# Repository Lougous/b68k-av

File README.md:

# Overview

This board provides audio and video capabilities to the b68k computer. Main components:
* CPLD for local bus decoding and FPGA configuration
* [flex FPGA](/doc/flex.md)
* SRAM 16-bits, 256kiB or 512 kiB
* video RAMDAC
* OPL2 audio chip

external interfaces: video (VGA, DIN 15 pins) and audio (3.5mm jack) 

# Memory mapping

The AVMGR CPLD decodes local bus accesses to address itself, the RAMDAC, the OPL2 or the flex FPGA.

| address range     | size   | memory area |
|:-----------------:|:------:|:-----:|
| 00000h  - 0007Fh  | 128B   | AVMGR registers. address bit 0 is ignored |
| 00080h  - 000FFh  | 128B   | flex registers |
| 00100h  - 0017Fh  | 128B   | RAMDAC registers. address bit 0 is ignored |
| 00180h  - 001FFh  | 128B   | OPL2 registers. address bit 0 is ignored |
| 00200h  - 07FFFh  | 512B*63 | mirrors x63 address range 000h-1FFh |
| 08000h -  0FFFFh  | 32kiB   | SRAM access (upper 32kiB, banking through flex register) |
| 10000h -  1FFFFh  | 64kiB   | SRAM access (banking through flex register) |

## AVMGR registers

These registers provide an interface to configure the flex FPGA. Address bit 0 is ignored, so that odd address target the same register as at even address.

| address offset    | name   | description |
|:-----------------:|:------:|:-----
| 00000h            | cfgnsts | bit 0: (r) flex nSTATUS signal<br>bit 1: (r) flex CONF_DONE signal<br>bit 6: (rw) flex nCONFIG signal<br>bit 7: (rw) flex reset signal (active low) |
| 00002h            | dat | bit 0: (rw) flex DAT0 signal<br>When this register is written, the flex DAT0 signal is driven and a pulse is generated on DCLK |
| 00004h            | dbg0 | spare register for debug purpose |
| 00006h            | dbg1 | spare register for debug purpose |

These registers mirror every 8 bytes.

## OPL2 registers

Provide access to the 2 OPL2 registers. Address bit 0 is ignored, so that odd address target the same register as at even address.

| address offset    | name   | description |
|:-----------------:|:------:|:-----
| 00000h            | regad | OPL2 Address (write) and status (read) register |
| 00002h            | regdt | OPL2 Data register |

## RAMDAC registers

Provide access to the RAMDAC registers (Bt476 / IMS G176 or compatible). Address bit 0 is ignored, so that odd address target the same register as at even address.

| address offset    | name   | description |
|:-----------------:|:------:|:-----
| 00000h            | ad_write | Address Register (RAM Write Mode) |
| 00002h            | color | Color Palette RAM |
| 00004h            | mask | Pixel read Mask Register |
| 00006h            | ad_read | Address Register (RAM Read Mode) |

## flex registers

See [flex FPGA](/doc/flex.md) documentation.

# BOM

| Reference  | Part |
|:-----------------:|:------:|
| RN1 | not populated |
| U1 | 74F245 |
| U2 | EPM7064SLC44-10 |
| U3 | MPC6002 |
| U4 | LM337 |
| U6 | EPF10K10LC84-4 |
| U7, U8 | 74F373 |
| U11 | YM3812 (OPL2) |
| U12 | KDA0476BCN-66 |
| D5 | BAT48 (shottky) |
| X1 or X3 | 25-MHz |

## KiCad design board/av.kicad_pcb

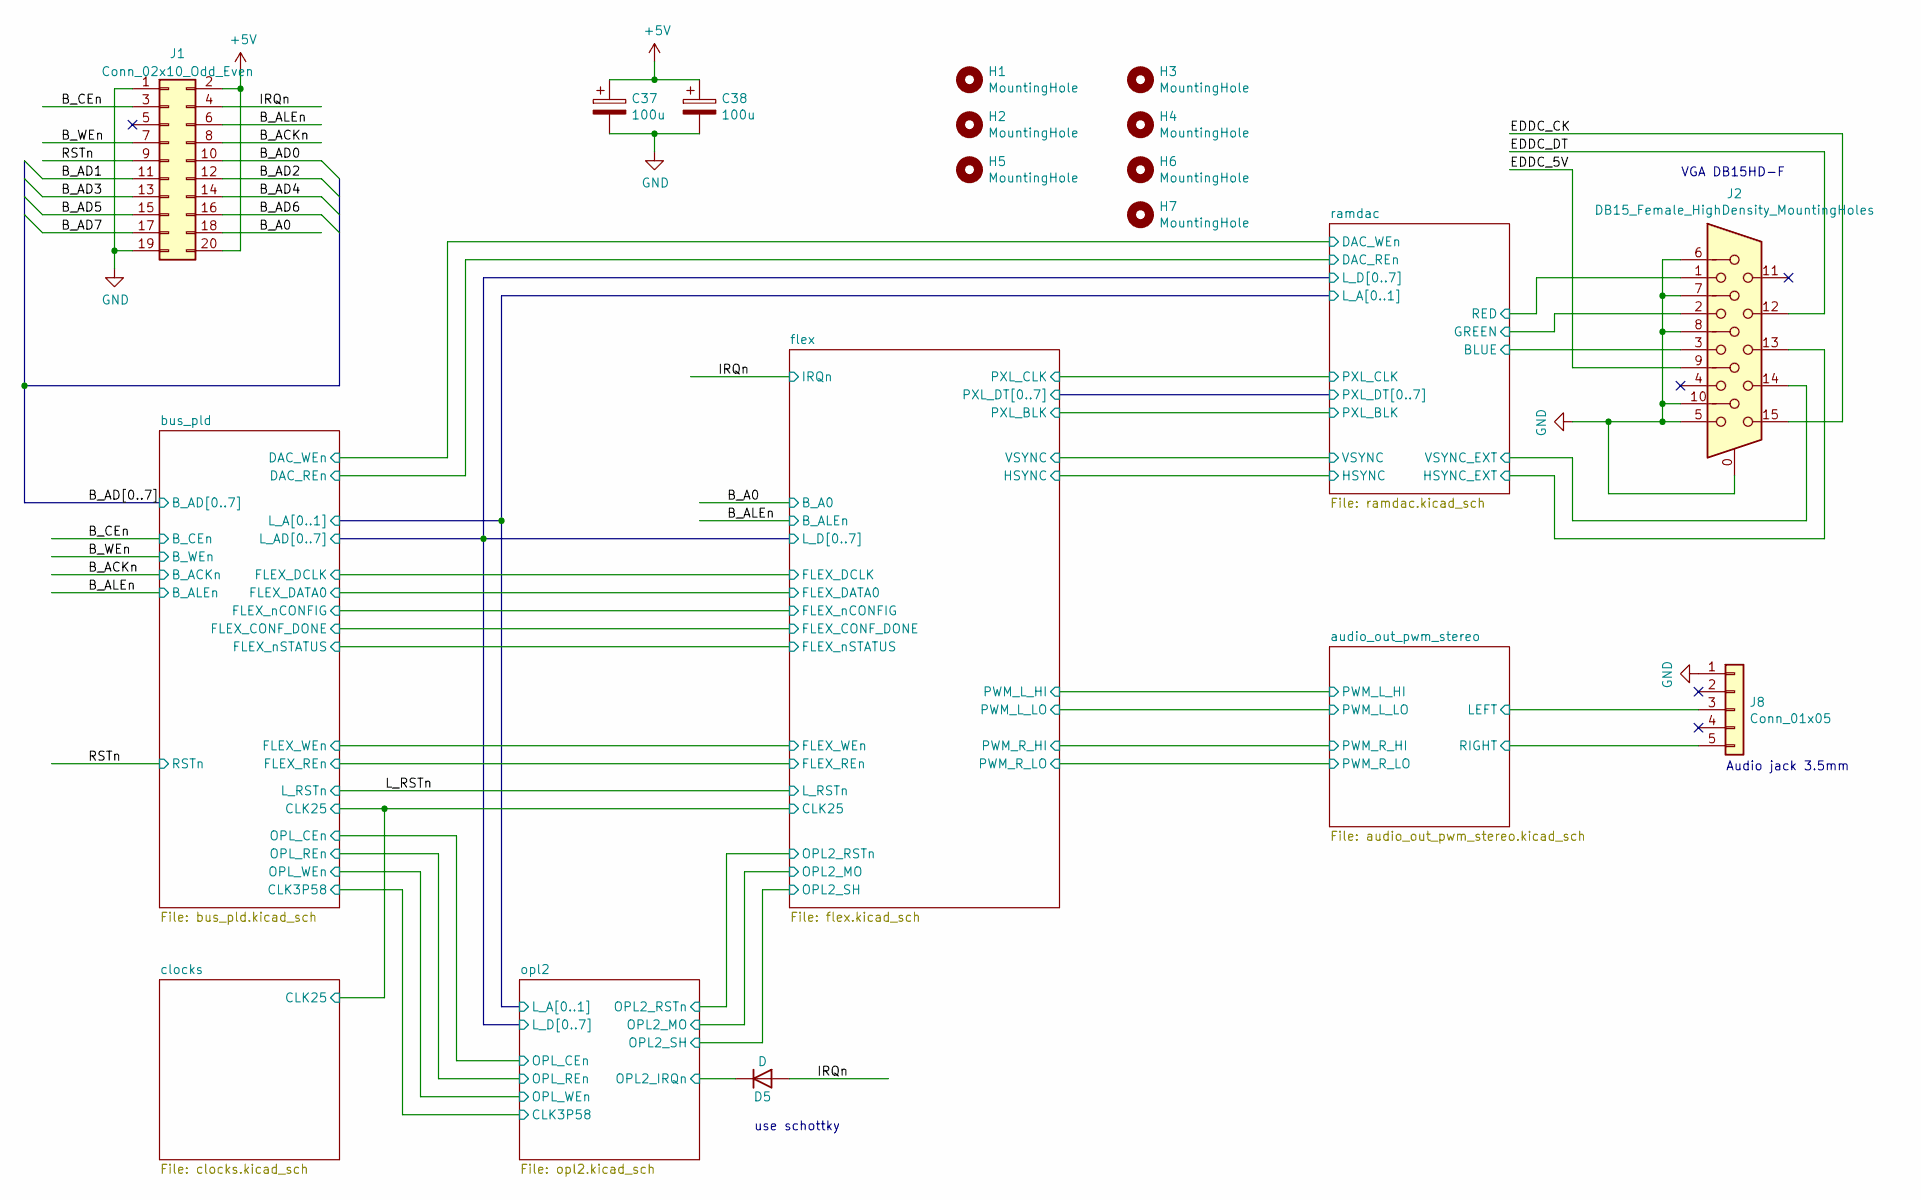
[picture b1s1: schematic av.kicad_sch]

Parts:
C37, C38: 100u; CP_Radial_D5.0mm_P2.00mm
D5: D; D_DO-34_SOD68_P7.62mm_Horizontal
H1, H2, H3, H4, H5, H6, H7: MountingHole; MountingHole_2.7mm_M2.5_DIN965_Pad
J1: Conn_02x10_Odd_Even; PinHeader_2x10_P2.54mm_Vertical
J2: DB15_Female_HighDensity_MountingHoles; DSUB-15-HD_Female_Horizontal_P2.29x1.98mm_EdgePinOffset3.03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
J8: Conn_01x05; ASJ-5-X_3.5mm_Jack

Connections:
+5V: C37.1, C38.1, J1.2, J1.20; also elsewhere on the board
/B_A0: J1.18; also elsewhere on the board
/B_ACKn: J1.8; also elsewhere on the board
/B_AD0: J1.10; also elsewhere on the board
/B_AD1: J1.11; also elsewhere on the board
/B_AD2: J1.12; also elsewhere on the board
/B_AD3: J1.13; also elsewhere on the board
/B_AD4: J1.14; also elsewhere on the board
/B_AD5: J1.15; also elsewhere on the board
/B_AD6: J1.16; also elsewhere on the board
/B_AD7: J1.17; also elsewhere on the board
/B_ALEn: J1.6; also elsewhere on the board
/B_CEn: J1.3; also elsewhere on the board
/B_WEn: J1.7; also elsewhere on the board
/EDDC_5V: J2.9
/EDDC_CK: J2.15
/EDDC_DT: J2.12
/IRQn: D5.2 (A), J1.4; also elsewhere on the board
/RSTn: J1.9; also elsewhere on the board
/audio_out_pwm_stereo/LEFT: J8.3; also elsewhere on the board
/audio_out_pwm_stereo/RIGHT: J8.5; also elsewhere on the board
/opl2/OPL2_IRQn: D5.1 (K); also elsewhere on the board
/ramdac/BLUE: J2.3; also elsewhere on the board
/ramdac/GREEN: J2.2; also elsewhere on the board
/ramdac/HSYNC_EXT: J2.13; also elsewhere on the board
/ramdac/RED: J2.1; also elsewhere on the board
/ramdac/VSYNC_EXT: J2.14; also elsewhere on the board
GND: C37.2, C38.2, J1.1, J1.19, J2.0, J2.5, J2.6, J2.7, J2.8, J2.10, J8.1; also elsewhere on the board

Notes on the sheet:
Audio jack 3.5mm
use schottky
VGA DB15HD-F

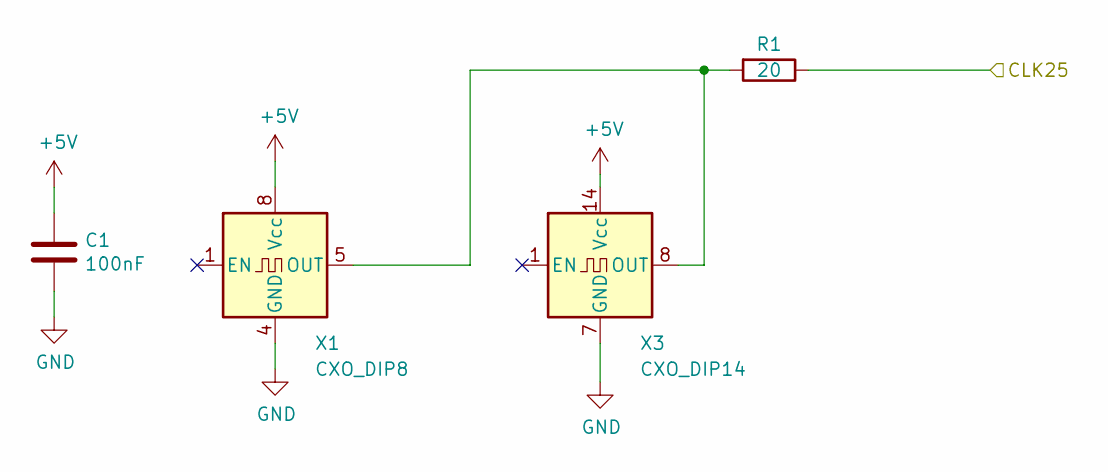
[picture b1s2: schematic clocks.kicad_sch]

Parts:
C1: 100nF; C_Disc_D4.3mm_W1.9mm_P5.00mm
R1: 20; R_Axial_DIN0204_L3.6mm_D1.6mm_P7.62mm_Horizontal
X1: CXO_DIP8; Oscillator_DIP-8
X3: CXO_DIP14; Oscillator_DIP-14

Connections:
+5V: C1.1, X1.8 (Vcc), X3.14 (Vcc); also elsewhere on the board
/flex/CLK25: R1.1; also elsewhere on the board
GND: C1.2, X1.4 (GND), X3.7 (GND); also elsewhere on the board
unnamed: R1.2, X1.5 (OUT), X3.8 (OUT)

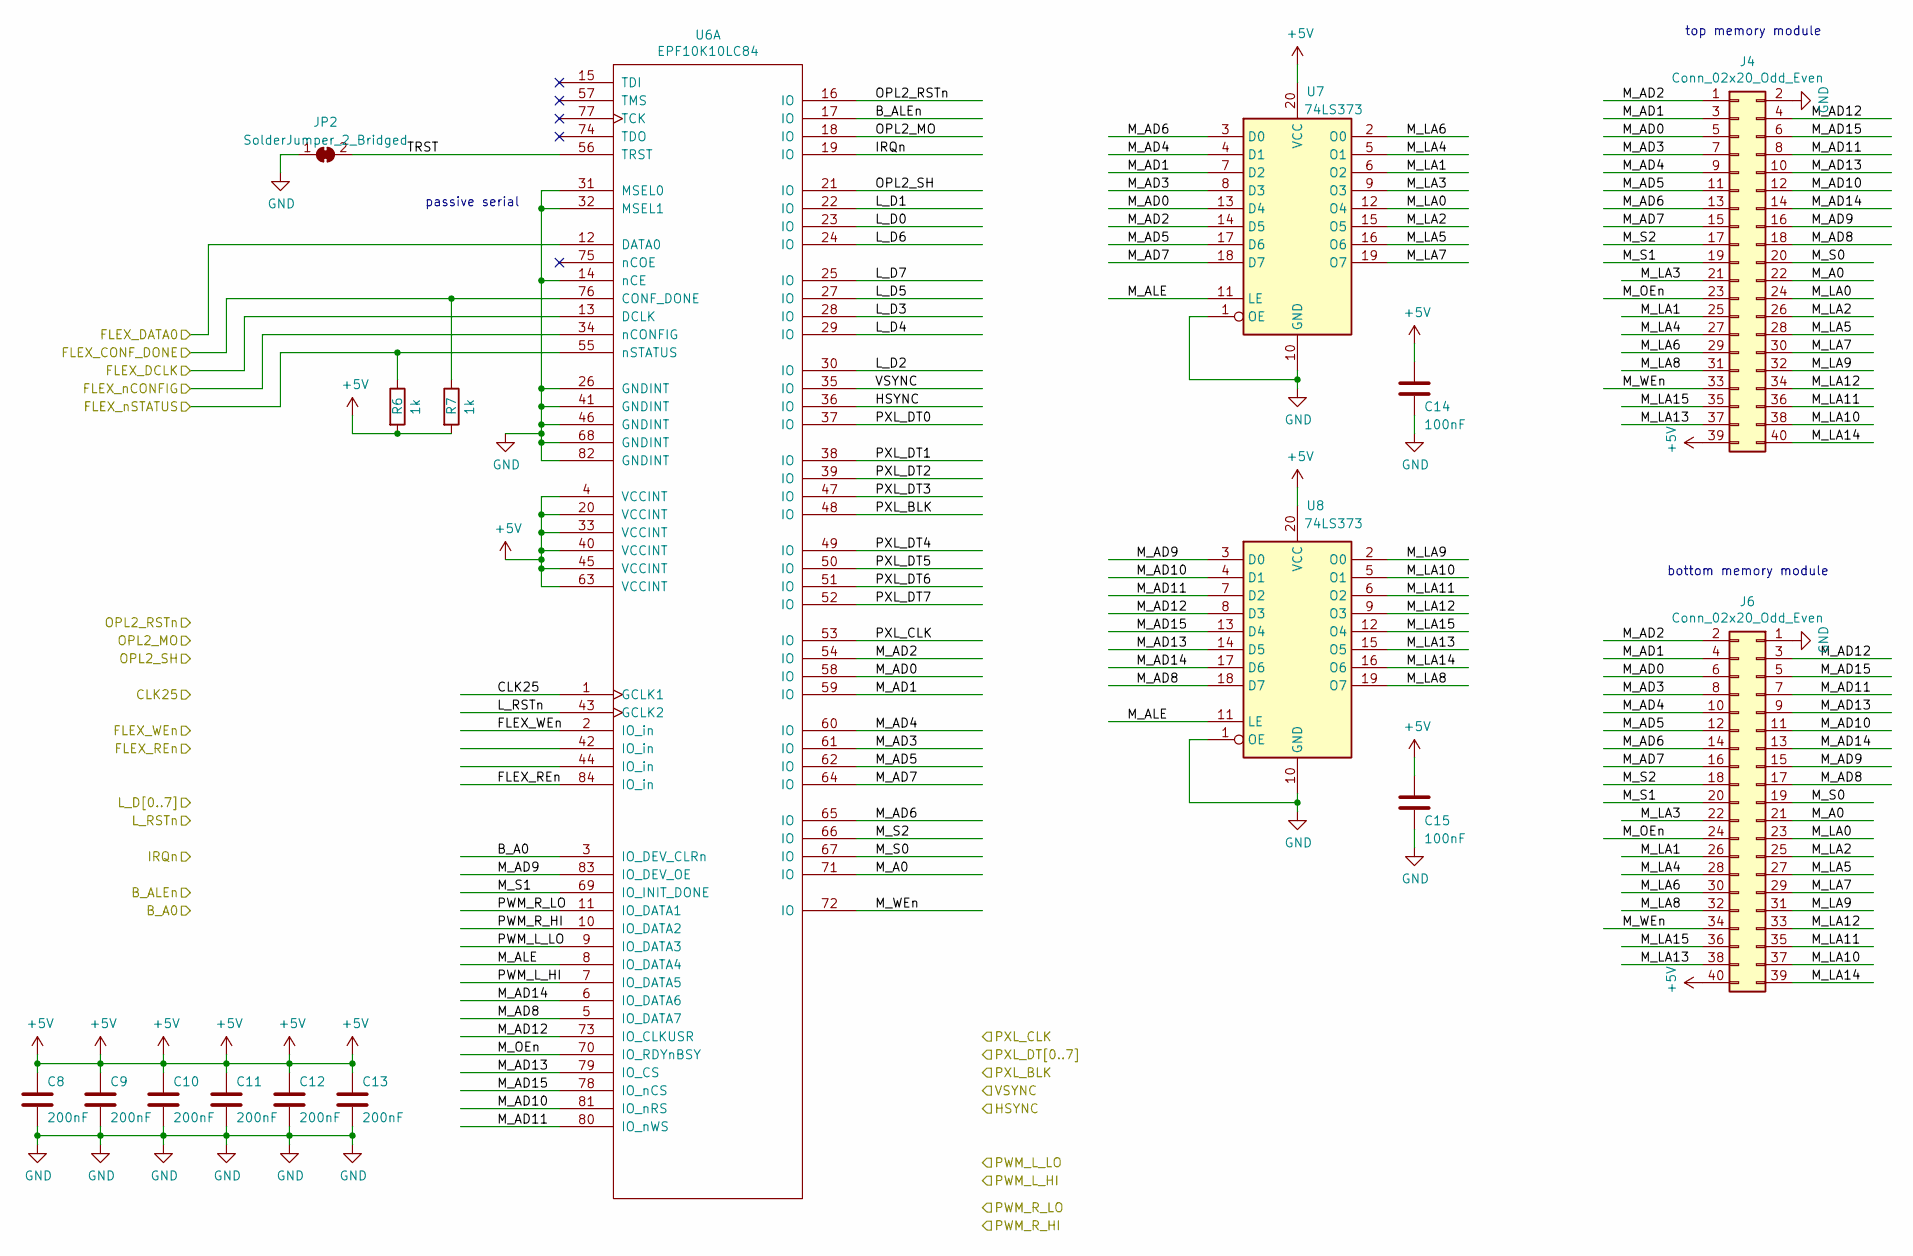
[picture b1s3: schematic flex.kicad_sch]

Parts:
C8, C9, C10, C11, C12, C13: 200nF; C_Disc_D4.3mm_W1.9mm_P5.00mm
C14, C15: 100nF; C_Disc_D4.3mm_W1.9mm_P5.00mm
J4, J6: Conn_02x20_Odd_Even; PinSocket_2x20_P2.00mm_Vertical_SMD
JP2: SolderJumper_2_Bridged; SolderJumper-2_P1.3mm_Bridged_RoundedPad1.0x1.5mm
R6, R7: 1k; R_Axial_DIN0204_L3.6mm_D1.6mm_P7.62mm_Horizontal
U6: EPF10K10LC84; PLCC-84_THT-Socket
U7, U8: 74LS373; DIP-20_W7.62mm_Socket

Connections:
+5V: C8.1, C9.1, C10.1, C11.1, C12.1, C13.1, C14.1, C15.1, J4.39, J6.40, R6.2, R7.2, U6.4 (VCCINT), U6.20 (VCCINT), U6.33 (VCCINT), U6.40 (VCCINT), U6.45 (VCCINT), U6.63 (VCCINT), U7.20 (VCC), U8.20 (VCC); also elsewhere on the board
/B_A0: U6.3 (IO_DEV_CLRn); also elsewhere on the board
/B_ALEn: U6.17 (IO); also elsewhere on the board
/IRQn: U6.19 (IO); also elsewhere on the board
/L_RSTn: U6.43 (GCLK2); also elsewhere on the board
/bus_pld/FLEX_CONF_DONE: R7.1, U6.76 (CONF_DONE); also elsewhere on the board
/bus_pld/FLEX_DATA0: U6.12 (DATA0); also elsewhere on the board
/bus_pld/FLEX_DCLK: U6.13 (DCLK); also elsewhere on the board
/bus_pld/FLEX_REn: U6.84 (IO_in); also elsewhere on the board
/bus_pld/FLEX_WEn: U6.2 (IO_in); also elsewhere on the board
/bus_pld/FLEX_nCONFIG: U6.34 (nCONFIG); also elsewhere on the board
/bus_pld/FLEX_nSTATUS: R6.1, U6.55 (nSTATUS); also elsewhere on the board
/bus_pld/L_AD0: U6.23 (IO); also elsewhere on the board
/bus_pld/L_AD1: U6.22 (IO); also elsewhere on the board
/bus_pld/L_AD2: U6.30 (IO); also elsewhere on the board
/bus_pld/L_AD3: U6.28 (IO); also elsewhere on the board
/bus_pld/L_AD4: U6.29 (IO); also elsewhere on the board
/bus_pld/L_AD5: U6.27 (IO); also elsewhere on the board
/bus_pld/L_AD6: U6.24 (IO); also elsewhere on the board
/bus_pld/L_AD7: U6.25 (IO); also elsewhere on the board
/flex/CLK25: U6.1 (GCLK1); also elsewhere on the board
/flex/HSYNC: U6.36 (IO); also elsewhere on the board
/flex/M_A0: J4.22, J6.21, U6.71 (IO)
/flex/M_AD0: J4.5, J6.6, U6.58 (IO), U7.13 (D4)
/flex/M_AD1: J4.3, J6.4, U6.59 (IO), U7.7 (D2)
/flex/M_AD2: J4.1, J6.2, U6.54 (IO), U7.14 (D5)
/flex/M_AD3: J4.7, J6.8, U6.61 (IO), U7.8 (D3)
/flex/M_AD4: J4.9, J6.10, U6.60 (IO), U7.4 (D1)
/flex/M_AD5: J4.11, J6.12, U6.62 (IO), U7.17 (D6)
/flex/M_AD6: J4.13, J6.14, U6.65 (IO), U7.3 (D0)
/flex/M_AD7: J4.15, J6.16, U6.64 (IO), U7.18 (D7)
/flex/M_AD8: J4.18, J6.17, U6.5 (IO_DATA7), U8.18 (D7)
/flex/M_AD9: J4.16, J6.15, U6.83 (IO_DEV_OE), U8.3 (D0)
/flex/M_AD10: J4.12, J6.11, U6.81 (IO_nRS), U8.4 (D1)
/flex/M_AD11: J4.8, J6.7, U6.80 (IO_nWS), U8.7 (D2)
/flex/M_AD12: J4.4, J6.3, U6.73 (IO_CLKUSR), U8.8 (D3)
/flex/M_AD13: J4.10, J6.9, U6.79 (IO_CS), U8.14 (D5)
/flex/M_AD14: J4.14, J6.13, U6.6 (IO_DATA6), U8.17 (D6)
/flex/M_AD15: J4.6, J6.5, U6.78 (IO_nCS), U8.13 (D4)
/flex/M_ALE: U6.8 (IO_DATA4), U7.11 (LE), U8.11 (LE)
/flex/M_LA0: J4.24, J6.23, U7.12 (O4)
/flex/M_LA1: J4.25, J6.26, U7.6 (O2)
/flex/M_LA2: J4.26, J6.25, U7.15 (O5)
/flex/M_LA3: J4.21, J6.22, U7.9 (O3)
/flex/M_LA4: J4.27, J6.28, U7.5 (O1)
/flex/M_LA5: J4.28, J6.27, U7.16 (O6)
/flex/M_LA6: J4.29, J6.30, U7.2 (O0)
/flex/M_LA7: J4.30, J6.29, U7.19 (O7)
/flex/M_LA8: J4.31, J6.32, U8.19 (O7)
/flex/M_LA9: J4.32, J6.31, U8.2 (O0)
/flex/M_LA10: J4.38, J6.37, U8.5 (O1)
/flex/M_LA11: J4.36, J6.35, U8.6 (O2)
/flex/M_LA12: J4.34, J6.33, U8.9 (O3)
/flex/M_LA13: J4.37, J6.38, U8.15 (O5)
/flex/M_LA14: J4.40, J6.39, U8.16 (O6)
/flex/M_LA15: J4.35, J6.36, U8.12 (O4)
/flex/M_OEn: J4.23, J6.24, U6.70 (IO_RDYnBSY)
/flex/M_S0: J4.20, J6.19, U6.67 (IO)
/flex/M_S1: J4.19, J6.20, U6.69 (IO_INIT_DONE)
/flex/M_S2: J4.17, J6.18, U6.66 (IO)
/flex/M_WEn: J4.33, J6.34, U6.72 (IO)
/flex/OPL2_MO: U6.18 (IO); also elsewhere on the board
/flex/OPL2_RSTn: U6.16 (IO); also elsewhere on the board
/flex/OPL2_SH: U6.21 (IO); also elsewhere on the board
/flex/PWM_L_HI: U6.7 (IO_DATA5); also elsewhere on the board
/flex/PWM_L_LO: U6.9 (IO_DATA3); also elsewhere on the board
/flex/PWM_R_HI: U6.10 (IO_DATA2); also elsewhere on the board
/flex/PWM_R_LO: U6.11 (IO_DATA1); also elsewhere on the board
/flex/PXL_BLK: U6.48 (IO); also elsewhere on the board
/flex/PXL_CLK: U6.53 (IO); also elsewhere on the board
/flex/PXL_DT0: U6.37 (IO); also elsewhere on the board
/flex/PXL_DT1: U6.38 (IO); also elsewhere on the board
/flex/PXL_DT2: U6.39 (IO); also elsewhere on the board
/flex/PXL_DT3: U6.47 (IO); also elsewhere on the board
/flex/PXL_DT4: U6.49 (IO); also elsewhere on the board
/flex/PXL_DT5: U6.50 (IO); also elsewhere on the board
/flex/PXL_DT6: U6.51 (IO); also elsewhere on the board
/flex/PXL_DT7: U6.52 (IO); also elsewhere on the board
/flex/TRST: JP2.2 (B), U6.56 (TRST)
/flex/VSYNC: U6.35 (IO); also elsewhere on the board
GND: C8.2, C9.2, C10.2, C11.2, C12.2, C13.2, C14.2, C15.2, J4.2, J6.1, JP2.1 (A), U6.14 (nCE), U6.26 (GNDINT), U6.31 (MSEL0), U6.32 (MSEL1), U6.41 (GNDINT), U6.46 (GNDINT), U6.68 (GNDINT), U6.82 (GNDINT), U7.1 (OE), U7.10 (GND), U8.1 (OE), U8.10 (GND); also elsewhere on the board

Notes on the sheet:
bottom memory module
passive serial
top memory module

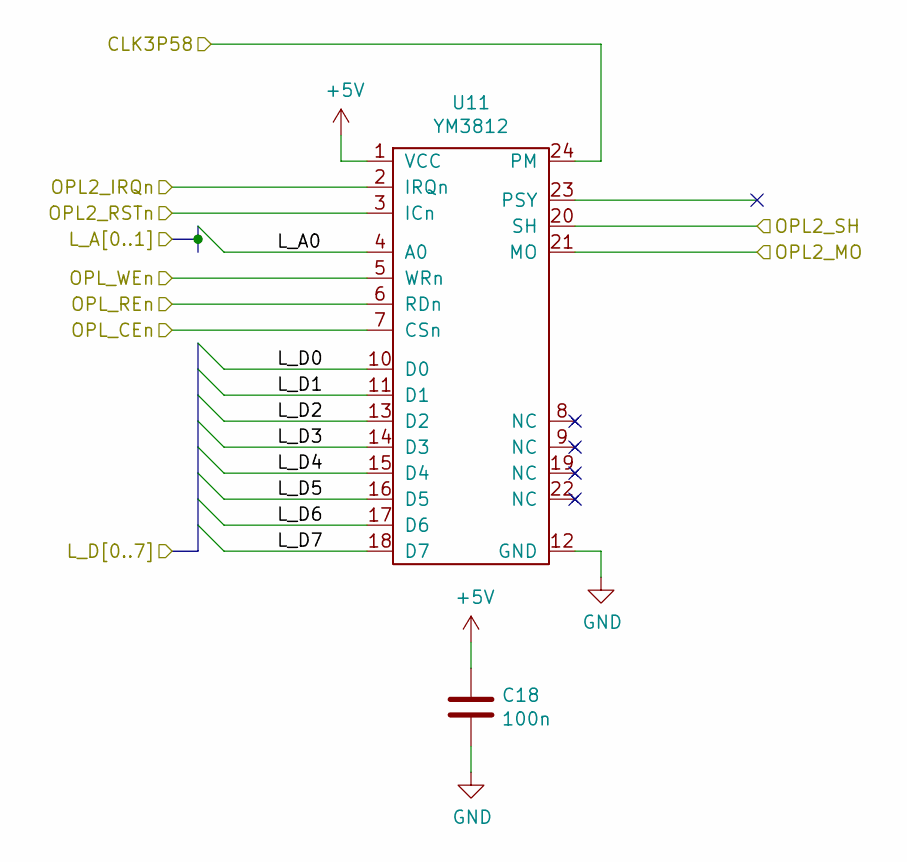
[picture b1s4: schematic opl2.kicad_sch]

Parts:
C18: 100n; C_Disc_D4.3mm_W1.9mm_P5.00mm
U11: YM3812; DIP-24_W15.24mm_Socket

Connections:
+5V: C18.1, U11.1 (VCC); also elsewhere on the board
/bus_pld/CLK3P58: U11.24 (PM); also elsewhere on the board
/bus_pld/L_A0: U11.4 (A0); also elsewhere on the board
/bus_pld/L_AD0: U11.10 (D0); also elsewhere on the board
/bus_pld/L_AD1: U11.11 (D1); also elsewhere on the board
/bus_pld/L_AD2: U11.13 (D2); also elsewhere on the board
/bus_pld/L_AD3: U11.14 (D3); also elsewhere on the board
/bus_pld/L_AD4: U11.15 (D4); also elsewhere on the board
/bus_pld/L_AD5: U11.16 (D5); also elsewhere on the board
/bus_pld/L_AD6: U11.17 (D6); also elsewhere on the board
/bus_pld/L_AD7: U11.18 (D7); also elsewhere on the board
/bus_pld/OPL_CEn: U11.7 (CSn); also elsewhere on the board
/bus_pld/OPL_REn: U11.6 (RDn); also elsewhere on the board
/bus_pld/OPL_WEn: U11.5 (WRn); also elsewhere on the board
/flex/OPL2_MO: U11.21 (MO); also elsewhere on the board
/flex/OPL2_RSTn: U11.3 (ICn); also elsewhere on the board
/flex/OPL2_SH: U11.20 (SH); also elsewhere on the board
/opl2/OPL2_IRQn: U11.2 (IRQn); also elsewhere on the board
GND: C18.2, U11.12 (GND); also elsewhere on the board

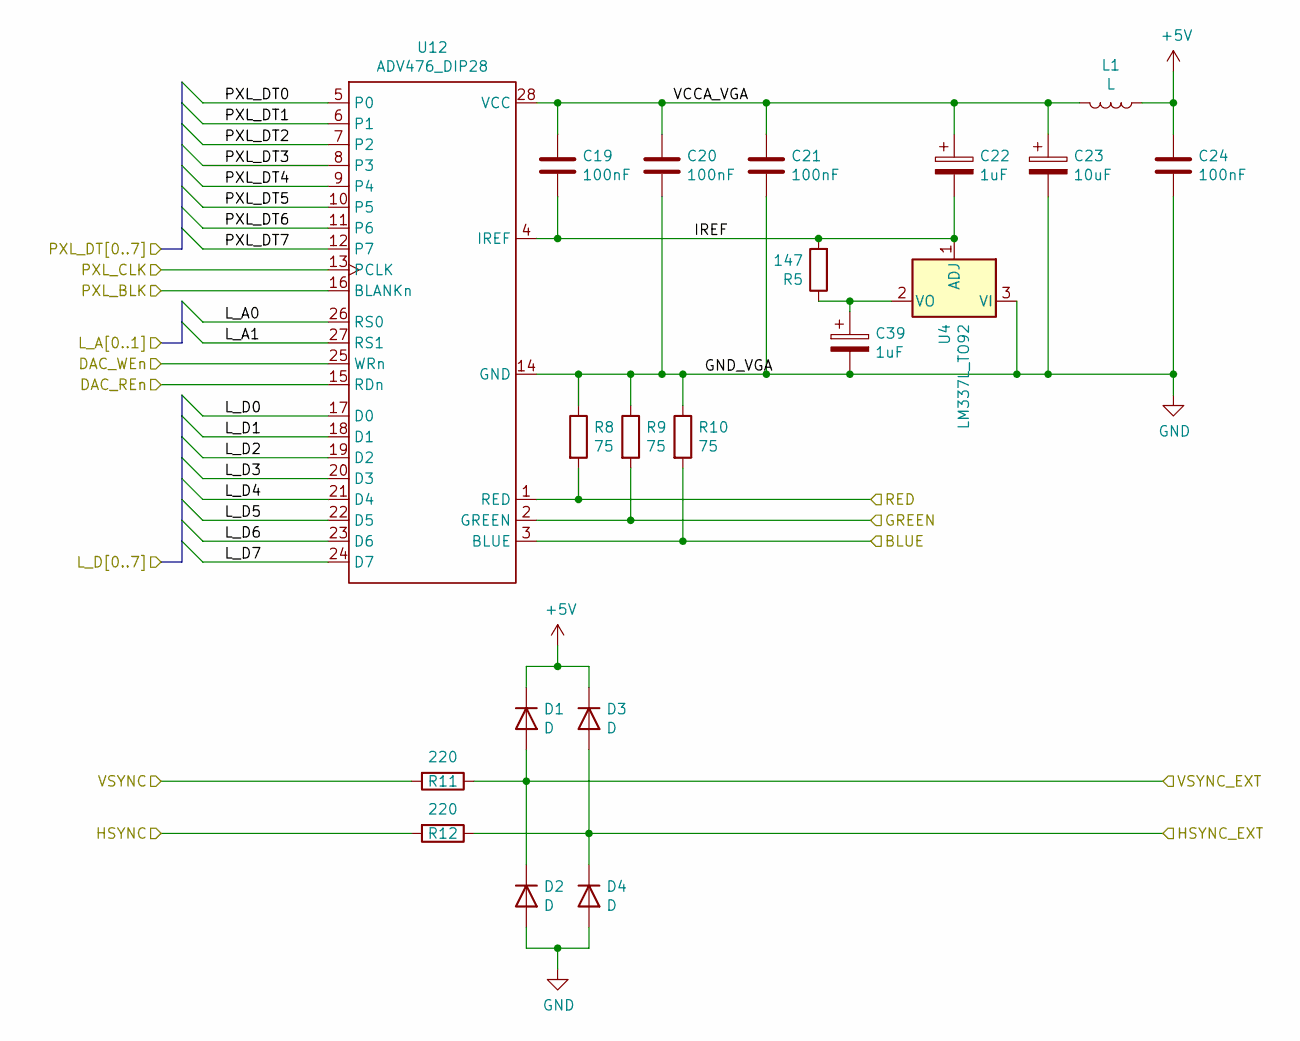
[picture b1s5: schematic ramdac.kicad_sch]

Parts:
C19, C20, C21, C24: 100nF; C_Disc_D4.3mm_W1.9mm_P5.00mm
C22, C39: 1uF; CP_Radial_Tantal_D4.5mm_P5.00mm
C23: 10uF; CP_Radial_Tantal_D4.5mm_P5.00mm
D1, D2, D3, D4: D; D_DO-34_SOD68_P7.62mm_Horizontal
L1: L; L_Axial_L5.3mm_D2.2mm_P2.54mm_Vertical_Vishay_IM-1
R5: 147; R_Axial_DIN0204_L3.6mm_D1.6mm_P2.54mm_Vertical
R8, R9, R10: 75; R_Axial_DIN0204_L3.6mm_D1.6mm_P7.62mm_Horizontal
R11, R12: 220; R_Axial_DIN0204_L3.6mm_D1.6mm_P7.62mm_Horizontal
U4: LM337L_TO92; TO-92_Inline_Narrow_Oval
U12: ADV476_DIP28; DIP-28_W15.24mm_Socket

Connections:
+5V: C24.1, D1.1 (K), D3.1 (K), L1.1; also elsewhere on the board
/bus_pld/DAC_REn: U12.15 (RDn); also elsewhere on the board
/bus_pld/DAC_WEn: U12.25 (WRn); also elsewhere on the board
/bus_pld/L_A0: U12.26 (RS0); also elsewhere on the board
/bus_pld/L_A1: U12.27 (RS1); also elsewhere on the board
/bus_pld/L_AD0: U12.17 (D0); also elsewhere on the board
/bus_pld/L_AD1: U12.18 (D1); also elsewhere on the board
/bus_pld/L_AD2: U12.19 (D2); also elsewhere on the board
/bus_pld/L_AD3: U12.20 (D3); also elsewhere on the board
/bus_pld/L_AD4: U12.21 (D4); also elsewhere on the board
/bus_pld/L_AD5: U12.22 (D5); also elsewhere on the board
/bus_pld/L_AD6: U12.23 (D6); also elsewhere on the board
/bus_pld/L_AD7: U12.24 (D7); also elsewhere on the board
/flex/HSYNC: R12.2; also elsewhere on the board
/flex/PXL_BLK: U12.16 (BLANKn); also elsewhere on the board
/flex/PXL_CLK: U12.13 (PCLK); also elsewhere on the board
/flex/PXL_DT0: U12.5 (P0); also elsewhere on the board
/flex/PXL_DT1: U12.6 (P1); also elsewhere on the board
/flex/PXL_DT2: U12.7 (P2); also elsewhere on the board
/flex/PXL_DT3: U12.8 (P3); also elsewhere on the board
/flex/PXL_DT4: U12.9 (P4); also elsewhere on the board
/flex/PXL_DT5: U12.10 (P5); also elsewhere on the board
/flex/PXL_DT6: U12.11 (P6); also elsewhere on the board
/flex/PXL_DT7: U12.12 (P7); also elsewhere on the board
/flex/VSYNC: R11.2; also elsewhere on the board
/ramdac/BLUE: R10.2, U12.3 (BLUE); also elsewhere on the board
/ramdac/GREEN: R9.2, U12.2 (GREEN); also elsewhere on the board
/ramdac/HSYNC_EXT: D3.2 (A), D4.1 (K), R12.1; also elsewhere on the board
/ramdac/IREF: C19.2, C22.2, R5.2, U4.1 (ADJ), U12.4 (IREF)
/ramdac/RED: R8.2, U12.1 (RED); also elsewhere on the board
/ramdac/VCCA_VGA: C19.1, C20.1, C21.1, C22.1, C23.1, L1.2, U12.28 (VCC)
/ramdac/VSYNC_EXT: D1.2 (A), D2.1 (K), R11.1; also elsewhere on the board
GND: C20.2, C21.2, C23.2, C24.2, C39.2, D2.2 (A), D4.2 (A), R8.1, R9.1, R10.1, U4.3 (VI), U12.14 (GND); also elsewhere on the board
unnamed: C39.1, R5.1, U4.2 (VO)

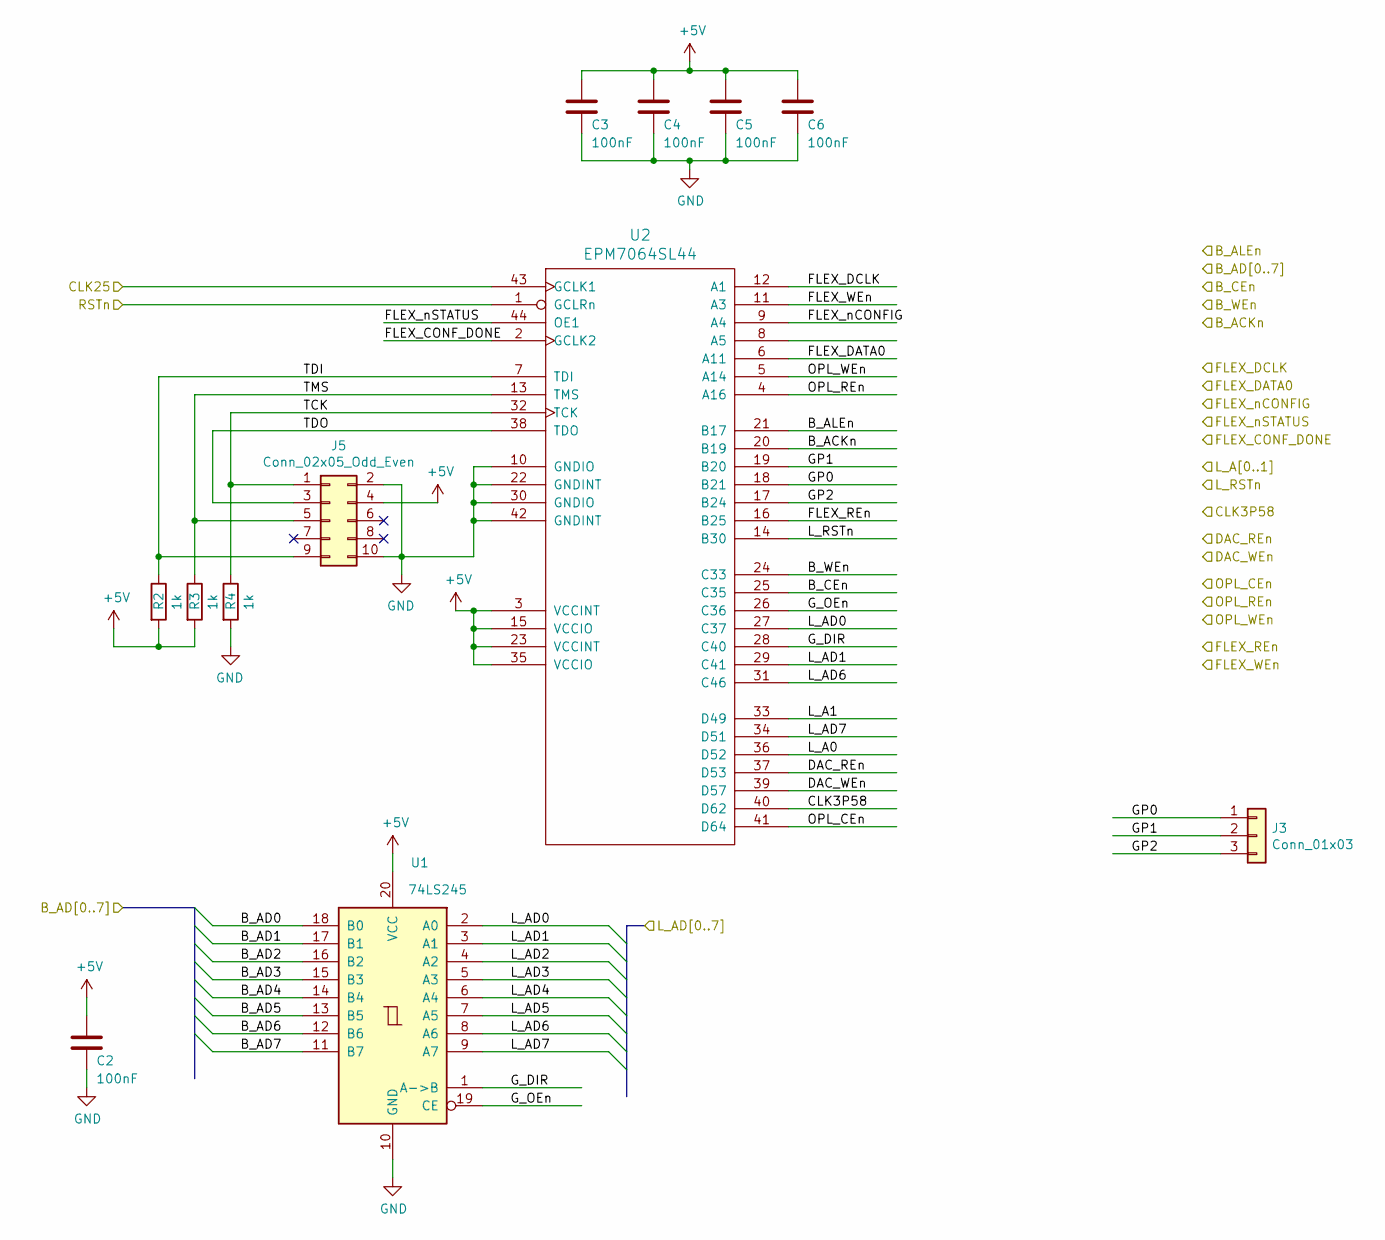
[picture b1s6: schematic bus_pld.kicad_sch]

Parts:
C2, C3, C4, C5, C6: 100nF; C_Disc_D4.3mm_W1.9mm_P5.00mm
J3: Conn_01x03; PinHeader_1x03_P2.54mm_Vertical
J5: Conn_02x05_Odd_Even; PinHeader_2x05_P2.54mm_Vertical
R2, R3, R4: 1k; R_Axial_DIN0204_L3.6mm_D1.6mm_P7.62mm_Horizontal
U1: 74LS245; DIP-20_W7.62mm_Socket
U2: EPM7064SL44; PLCC-44_THT-Socket

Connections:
+5V: C2.1, C3.1, C4.1, C5.1, C6.1, J5.4, R2.2, R3.2, U1.20 (VCC), U2.3 (VCCINT), U2.15 (VCCIO), U2.23 (VCCINT), U2.35 (VCCIO); also elsewhere on the board
/B_ACKn: U2.20 (B19); also elsewhere on the board
/B_AD0: U1.18 (B0); also elsewhere on the board
/B_AD1: U1.17 (B1); also elsewhere on the board
/B_AD2: U1.16 (B2); also elsewhere on the board
/B_AD3: U1.15 (B3); also elsewhere on the board
/B_AD4: U1.14 (B4); also elsewhere on the board
/B_AD5: U1.13 (B5); also elsewhere on the board
/B_AD6: U1.12 (B6); also elsewhere on the board
/B_AD7: U1.11 (B7); also elsewhere on the board
/B_ALEn: U2.21 (B17); also elsewhere on the board
/B_CEn: U2.25 (C35); also elsewhere on the board
/B_WEn: U2.24 (C33); also elsewhere on the board
/L_RSTn: U2.14 (B30); also elsewhere on the board
/RSTn: U2.1 (GCLRn); also elsewhere on the board
/bus_pld/CLK3P58: U2.40 (D62); also elsewhere on the board
/bus_pld/DAC_REn: U2.37 (D53); also elsewhere on the board
/bus_pld/DAC_WEn: U2.39 (D57); also elsewhere on the board
/bus_pld/FLEX_CONF_DONE: U2.2 (GCLK2); also elsewhere on the board
/bus_pld/FLEX_DATA0: U2.6 (A11); also elsewhere on the board
/bus_pld/FLEX_DCLK: U2.12 (A1); also elsewhere on the board
/bus_pld/FLEX_REn: U2.16 (B25); also elsewhere on the board
/bus_pld/FLEX_WEn: U2.11 (A3); also elsewhere on the board
/bus_pld/FLEX_nCONFIG: U2.9 (A4); also elsewhere on the board
/bus_pld/FLEX_nSTATUS: U2.44 (OE1); also elsewhere on the board
/bus_pld/GP0: J3.1, U2.18 (B21)
/bus_pld/GP1: J3.2, U2.19 (B20)
/bus_pld/GP2: J3.3, U2.17 (B24)
/bus_pld/G_DIR: U1.1 (A->B), U2.28 (C40)
/bus_pld/G_OEn: U1.19 (CE), U2.26 (C36)
/bus_pld/L_A0: U2.36 (D52); also elsewhere on the board
/bus_pld/L_A1: U2.33 (D49); also elsewhere on the board
/bus_pld/L_AD0: U1.2 (A0), U2.27 (C37); also elsewhere on the board
/bus_pld/L_AD1: U1.3 (A1), U2.29 (C41); also elsewhere on the board
/bus_pld/L_AD2: U1.4 (A2); also elsewhere on the board
/bus_pld/L_AD3: U1.5 (A3); also elsewhere on the board
/bus_pld/L_AD4: U1.6 (A4); also elsewhere on the board
/bus_pld/L_AD5: U1.7 (A5); also elsewhere on the board
/bus_pld/L_AD6: U1.8 (A6), U2.31 (C46); also elsewhere on the board
/bus_pld/L_AD7: U1.9 (A7), U2.34 (D51); also elsewhere on the board
/bus_pld/OPL_CEn: U2.41 (D64); also elsewhere on the board
/bus_pld/OPL_REn: U2.4 (A16); also elsewhere on the board
/bus_pld/OPL_WEn: U2.5 (A14); also elsewhere on the board
/bus_pld/TCK: J5.1, R4.1, U2.32 (TCK)
/bus_pld/TDI: J5.9, R2.1, U2.7 (TDI)
/bus_pld/TDO: J5.3, U2.38 (TDO)
/bus_pld/TMS: J5.5, R3.1, U2.13 (TMS)
/flex/CLK25: U2.43 (GCLK1); also elsewhere on the board
GND: C2.2, C3.2, C4.2, C5.2, C6.2, J5.2, J5.10, R4.2, U1.10 (GND), U2.10 (GNDIO), U2.22 (GNDINT), U2.30 (GNDIO), U2.42 (GNDINT); also elsewhere on the board

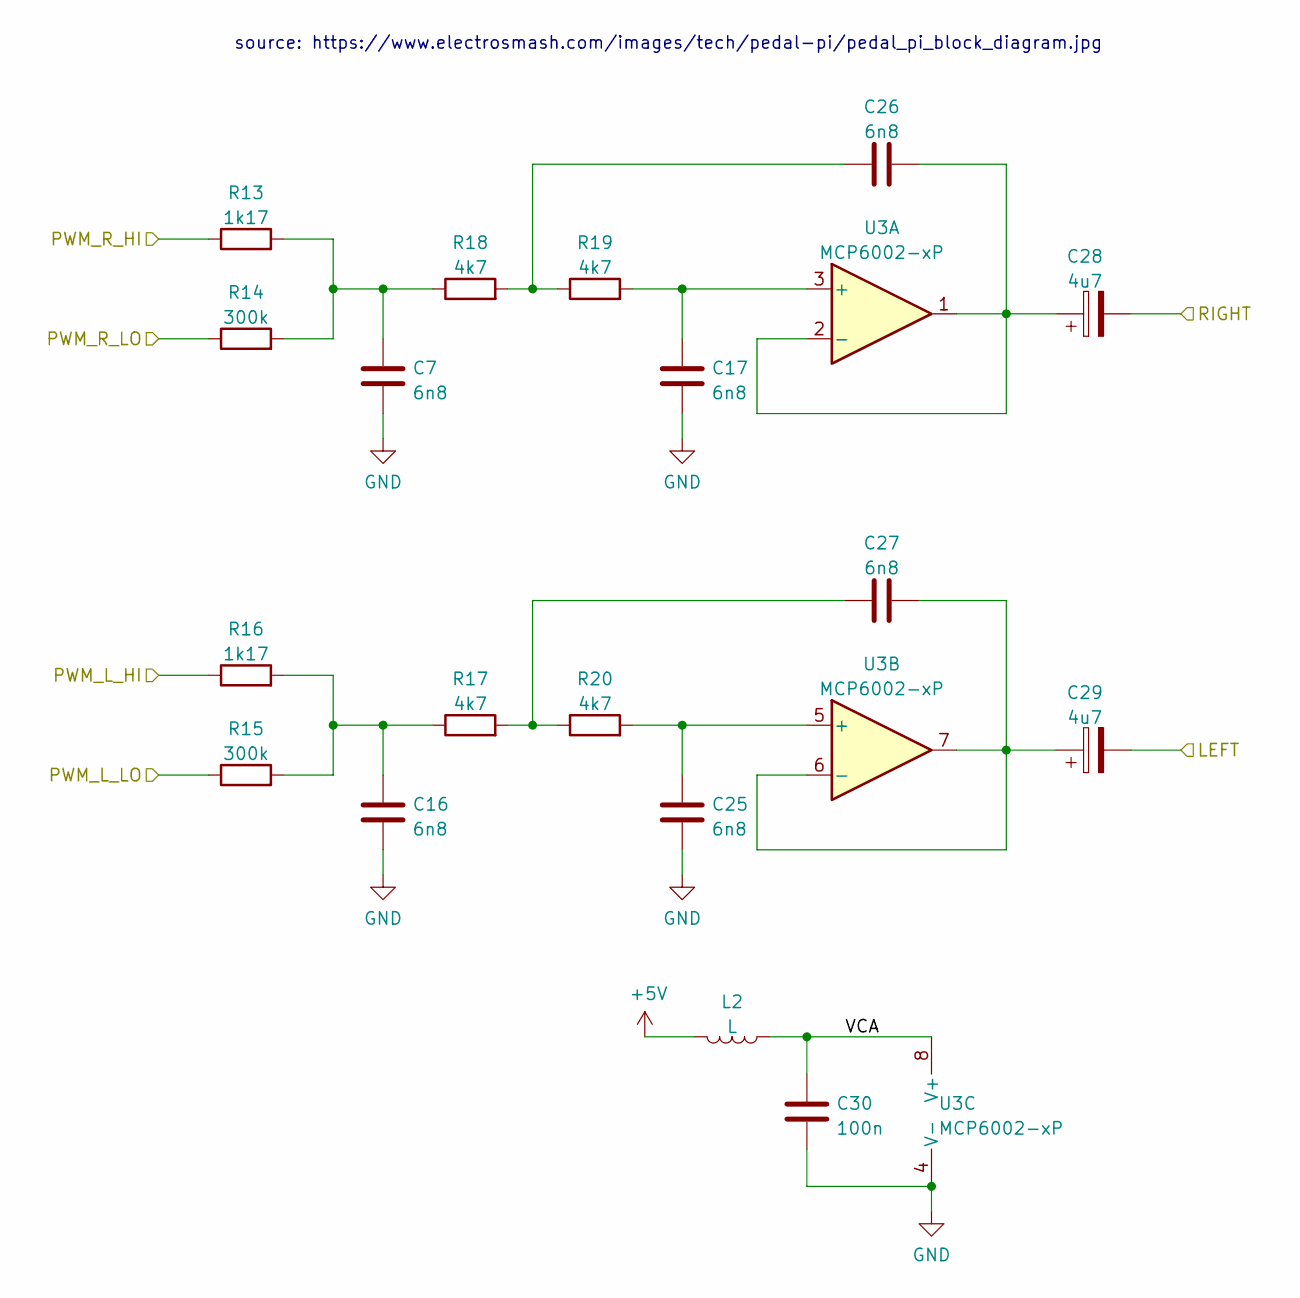
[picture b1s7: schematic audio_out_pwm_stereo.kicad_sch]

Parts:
C7, C16, C17, C25, C26, C27: 6n8; C_Disc_D4.3mm_W1.9mm_P5.00mm
C28, C29: 4u7; CP_Radial_D5.0mm_P2.00mm
C30: 100n; C_Disc_D4.3mm_W1.9mm_P5.00mm
L2: L; L_Axial_L5.3mm_D2.2mm_P2.54mm_Vertical_Vishay_IM-1
R13, R16: 1k17; R_Axial_DIN0204_L3.6mm_D1.6mm_P7.62mm_Horizontal
R14, R15: 300k; R_Axial_DIN0204_L3.6mm_D1.6mm_P7.62mm_Horizontal
R17, R18, R19, R20: 4k7; R_Axial_DIN0204_L3.6mm_D1.6mm_P7.62mm_Horizontal
U3: MCP6002-xP; DIP-8_W7.62mm_Socket

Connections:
+5V: L2.2; also elsewhere on the board
/audio_out_pwm_stereo/LEFT: C29.2; also elsewhere on the board
/audio_out_pwm_stereo/RIGHT: C28.2; also elsewhere on the board
/audio_out_pwm_stereo/VCA: C30.1, L2.1, U3.8 (V+)
/flex/PWM_L_HI: R16.1; also elsewhere on the board
/flex/PWM_L_LO: R15.1; also elsewhere on the board
/flex/PWM_R_HI: R13.1; also elsewhere on the board
/flex/PWM_R_LO: R14.1; also elsewhere on the board
GND: C7.2, C16.2, C17.2, C25.2, C30.2, U3.4 (V-); also elsewhere on the board
unnamed: C7.1, R13.2, R14.2, R18.1
unnamed: C16.1, R15.2, R16.2, R17.1
unnamed: C17.1, R19.2, U3.3 (+)
unnamed: C25.1, R20.2, U3.5 (+)
unnamed: C26.1, R18.2, R19.1
unnamed: C26.2, C28.1, U3.1, U3.2 (-)
unnamed: C27.1, R17.2, R20.1
unnamed: C27.2, C29.1, U3.6 (-), U3.7

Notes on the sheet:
source: https://www.electrosmash.com/images/tech/pedal-pi/pedal_pi_block_diagram.jpg

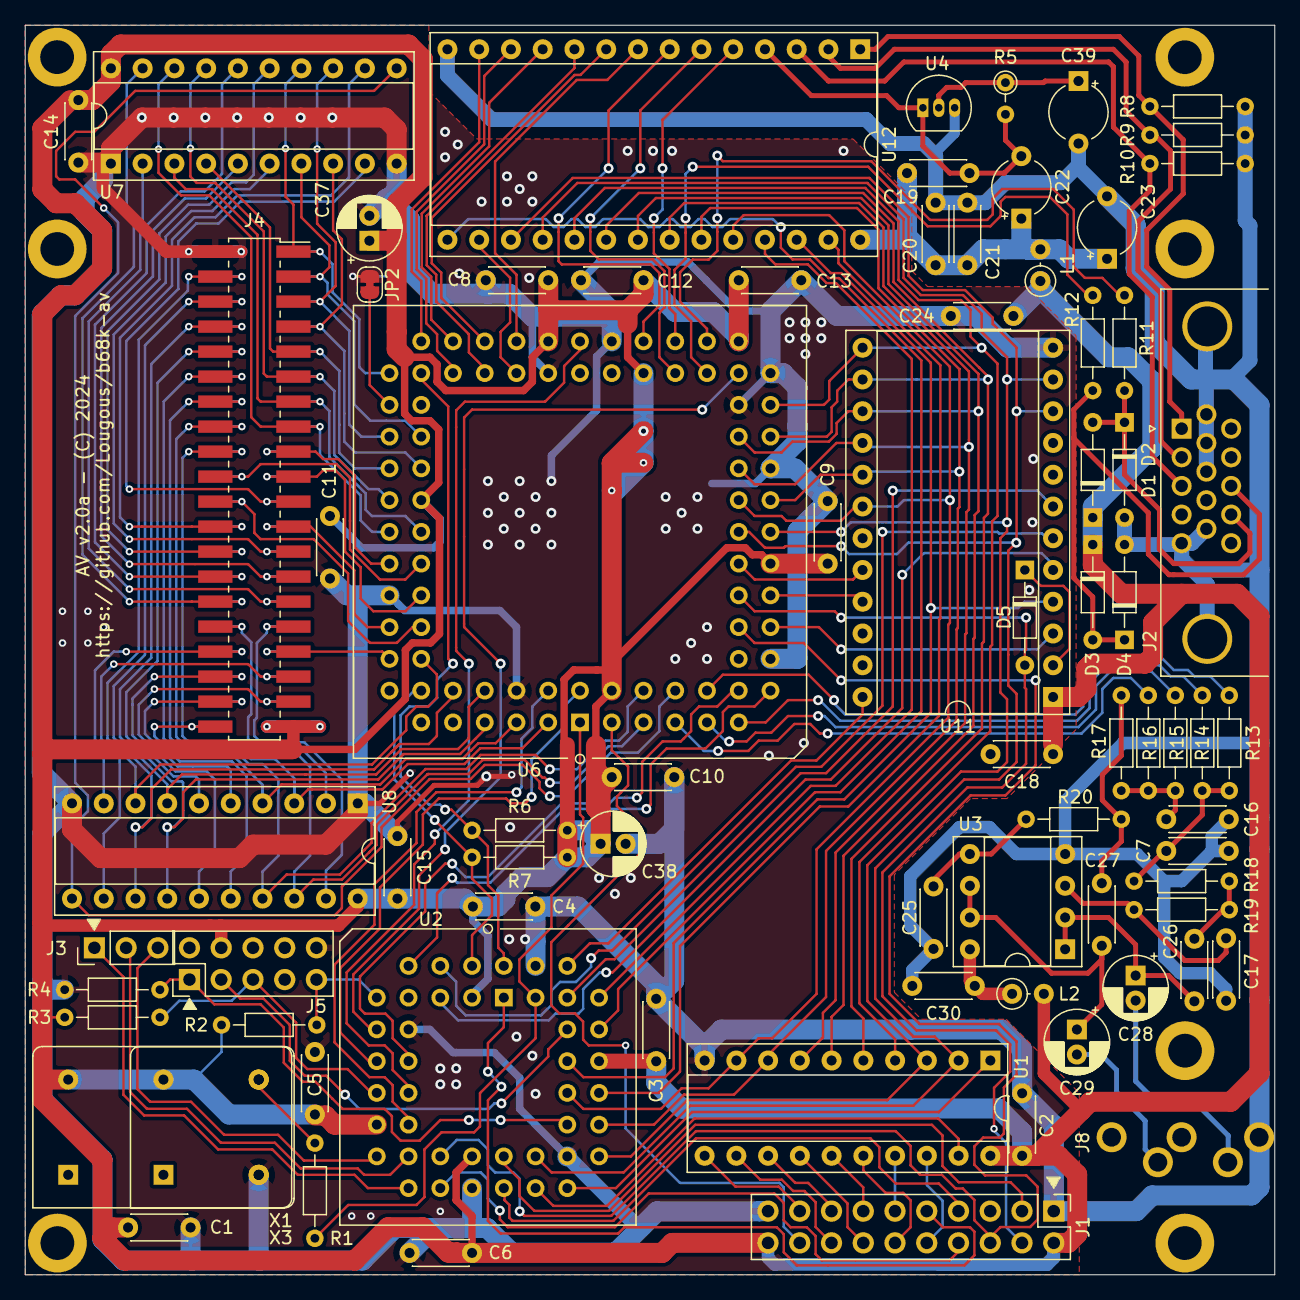
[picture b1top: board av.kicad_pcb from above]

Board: 2 copper layers, 100.0 x 100.0 mm, 86 parts (1 on the bottom side), 131 nets.

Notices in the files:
board/av.kicad_pcb:
AV v2.0a - (C) 2024
